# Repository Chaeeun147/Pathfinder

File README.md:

# Pathfinder
A custom PCB controller board and fidget!

I made this project because I love fidget toys, and I found it intriguing that I could use it as both a piece of tech AND a fidget toy.
My pathfinder is also programmed, so when I press different buttons or button combinations, it turns on different LED lights!

Schematic:

PCB:

3D Viewer:

BOM:
| Part Name | Quantity | Description | Cost | Link  |
| --------- | -------- | ----------- | ---- | - |
| LED | 10 | Light | $1.17 | https://www.aliexpress.com/item/32759416007.html?spm=a2g0o.productlist.main.25.5ad45d4fBpD18Y&algo_pvid=c7d3ffdf-054c-4a00-8b1f-7dc1258b8f89&algo_exp_id=c7d3ffdf-054c-4a00-8b1f-7dc1258b8f89-24&pdp_ext_f=%7B%22order%22%3A%2263%22%2C%22spu_best_type%22%3A%22price%22%2C%22eval%22%3A%221%22%2C%22fromPage%22%3A%22search%22%7D&pdp_npi=6%40dis%21CAD%212.47%211.60%21%21%211.76%211.14%21%402103110517740490152535062ebe05%2112000027866463708%21sea%21CA%217451194651%21ABX%211%210%21n_tag%3A-29910%3Bd%3A8fd05d1b%3Bm03_new_user%3A-29895%3BpisId%3A5000000197831969&curPageLogUid=rJeiEFxpdOuU&utparam-url=scene%3Asearch%7Cquery_from%3A%7Cx_object_id%3A32759416007%7C_p_origin_prod%3A |
| Resistor | 100 | Resistor | $0.73 | https://www.aliexpress.com/item/1005006040209297.html?spm=a2g0o.productlist.main.1.44fe7785qfn6Bm&algo_pvid=6d8afb23-2538-424a-ae4a-d31f3bcf2f64&algo_exp_id=6d8afb23-2538-424a-ae4a-d31f3bcf2f64-0&pdp_ext_f=%7B%22order%22%3A%22341%22%2C%22spu_best_type%22%3A%22price%22%2C%22eval%22%3A%221%22%2C%22fromPage%22%3A%22search%22%7D&pdp_npi=6%40dis%21CAD%210.72%210.72%21%21%210.51%210.51%21%402101e80317740488821005309e1bc6%2112000035442807620%21sea%21CA%217451194651%21ABX%211%210%21n_tag%3A-29910%3Bd%3A8fd05d1b%3Bm03_new_user%3A-29895&curPageLogUid=NUwI7MvNd3uo&utparam-url=scene%3Asearch%7Cquery_from%3A%7Cx_object_id%3A1005006040209297%7C_p_origin_prod%3A |
| Xiao RP 2040 | 1 | PCB | $3.59 |https://www.aliexpress.com/item/1005003908237026.html?spm=a2g0o.cart.0.0.6df938dabXCDew&mp=1&pdp_npi=6%40dis%21CAD%21CAD+11.73%21CAD+4.93%21%21CAD+4.75%21%21%21%40210328df17740487064442830e3672%2112000056511616306%21ct%21CA%217451194651%21%216%210%21) |
| Cherry MX Switch | 10 | Input | $2.60 | https://www.aliexpress.com/item/1005008811335051.html?spm=a2g0o.cart.0.0.6df938dabXCDew&mp=1&pdp_npi=6%40dis%21CAD%21CAD+52.73%21CAD+45.79%21%21CAD+44.15%21%21%21%40210328df17740487064442830e3672%2112000046764301536%21ct%21CA%217451194651%21%211%210%21 |
| Custom PCB | 5 | PCB | $2.00 | https://jlcpcb.com/ |

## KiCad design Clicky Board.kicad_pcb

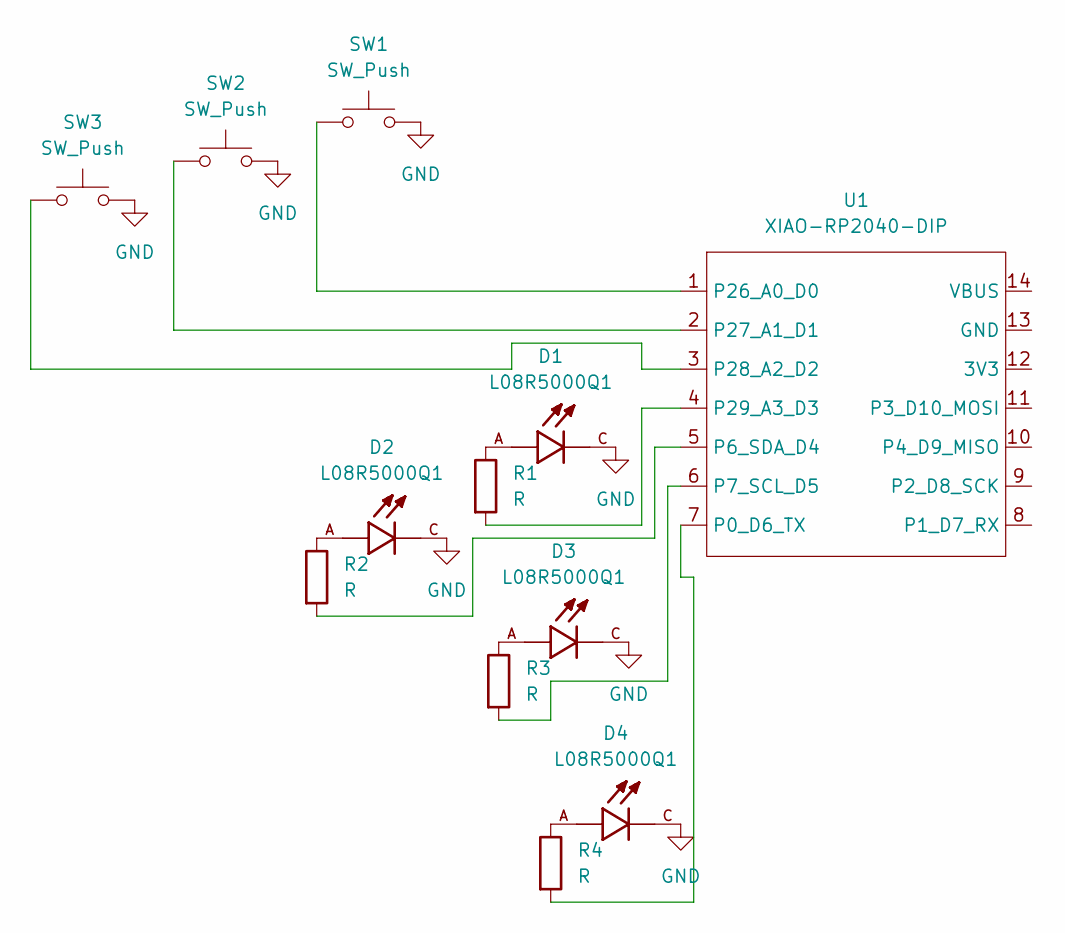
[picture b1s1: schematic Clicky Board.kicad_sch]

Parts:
D1, D2, D3, D4: L08R5000Q1; LEDRD254W57D500H1070; PARTREV NA
R1, R2, R3, R4: R; R_Axial_DIN0204_L3.6mm_D1.6mm_P5.08mm_Horizontal
SW1, SW2, SW3: SW_Push; SW_Cherry_MX_1.00u_PCB
U1: XIAO-RP2040-DIP

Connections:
GND: D1.C, D2.C, D3.C, D4.C, SW1.2, SW2.2, SW3.2
unnamed: D1.A, R1.1
unnamed: D2.A, R2.1
unnamed: D3.A, R3.1
unnamed: D4.A, R4.1
unnamed: R4.2, U1.7 (P0_D6_TX)
unnamed: R2.2, U1.5 (P6_SDA_D4)
unnamed: R3.2, U1.6 (P7_SCL_D5)
unnamed: SW1.1, U1.1 (P26_A0_D0)
unnamed: SW2.1, U1.2 (P27_A1_D1)
unnamed: SW3.1, U1.3 (P28_A2_D2)
unnamed: R1.2, U1.4 (P29_A3_D3)

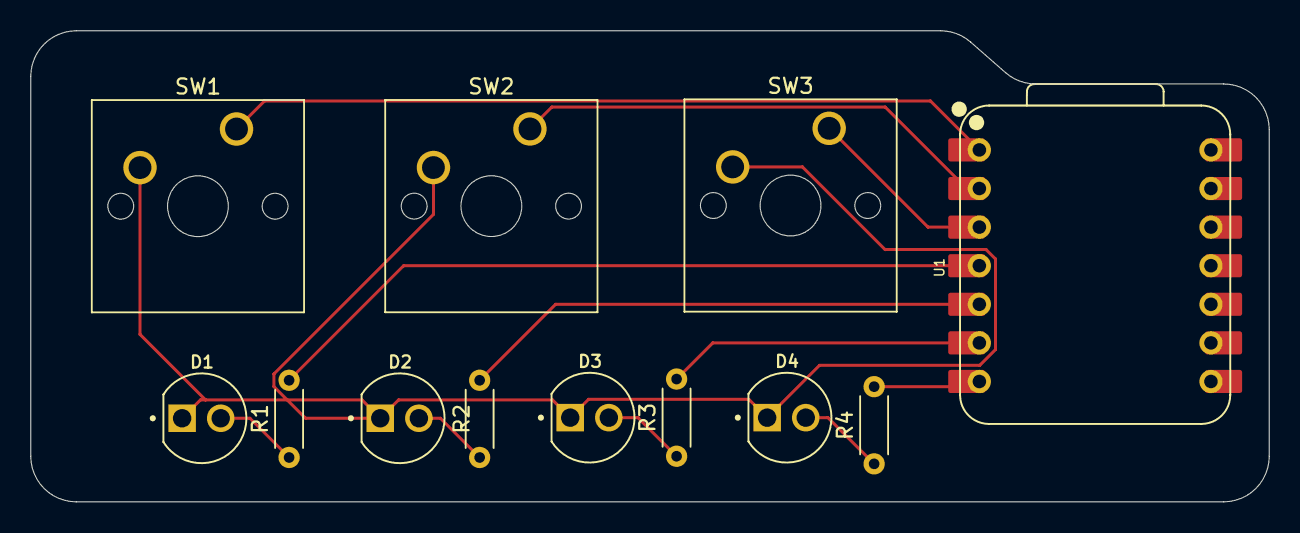
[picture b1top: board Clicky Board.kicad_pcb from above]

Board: 2 copper layers, 81.5 x 31.0 mm, 12 parts (0 on the bottom side), 12 nets.

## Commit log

2026-04-16 Enhance README with project details and images
    Added project description, images, and details about functionality.
2026-04-22 Add BOM section to README
    Added a Bill of Materials (BOM) section with details on components used, including quantities, descriptions, costs, and links.
2026-04-22 Fix BOM section formatting in README.md
2026-04-22 Fix table header typo in BOM section
2026-04-22 Update Cherry MX Switches entry in README
2026-04-22 Correct link formatting for Xiao RP 2040
    Fixed formatting for the Xiao RP 2040 link in the table.
